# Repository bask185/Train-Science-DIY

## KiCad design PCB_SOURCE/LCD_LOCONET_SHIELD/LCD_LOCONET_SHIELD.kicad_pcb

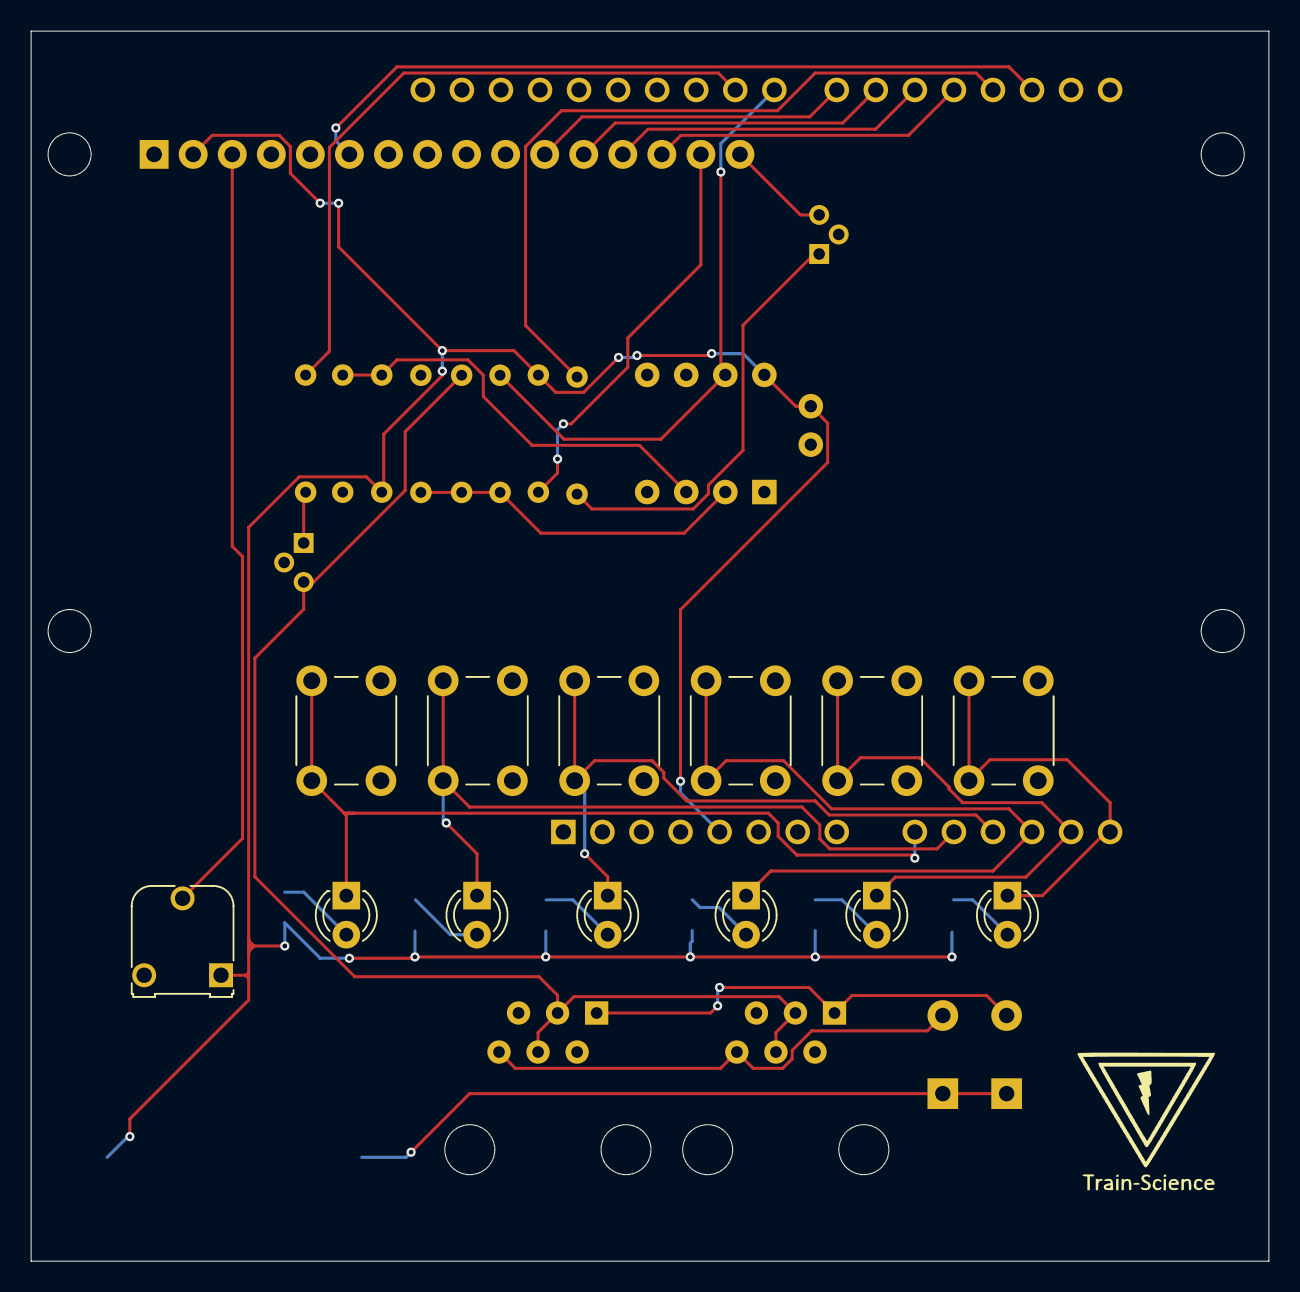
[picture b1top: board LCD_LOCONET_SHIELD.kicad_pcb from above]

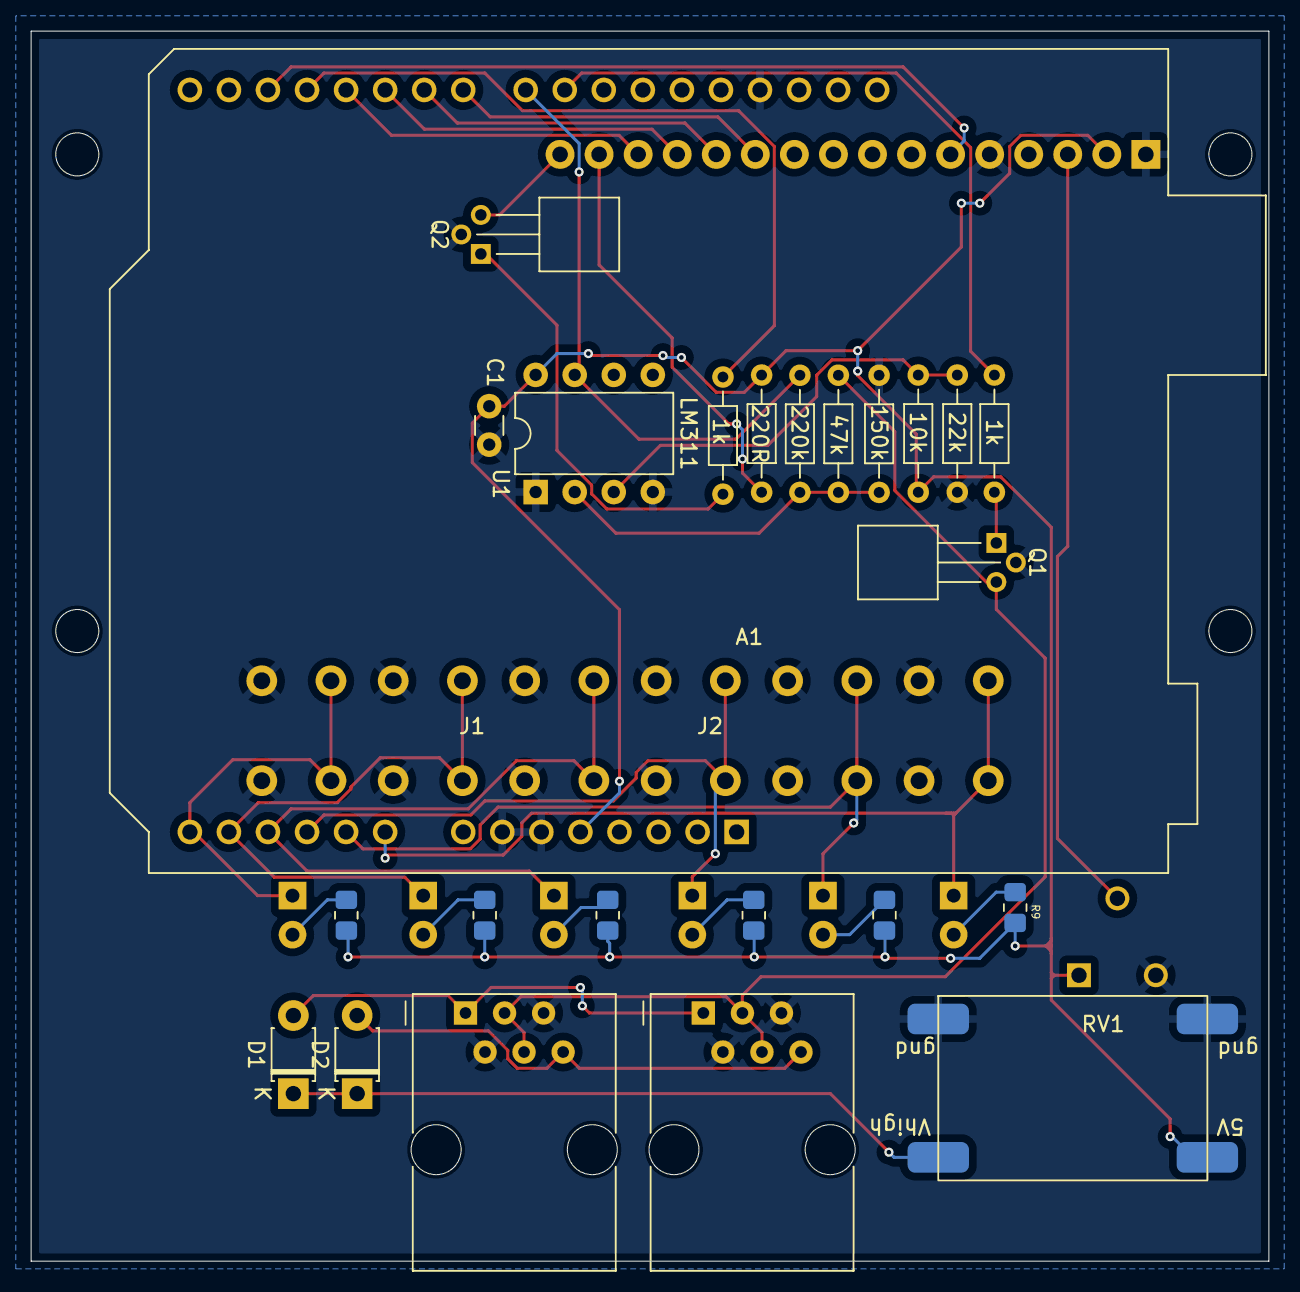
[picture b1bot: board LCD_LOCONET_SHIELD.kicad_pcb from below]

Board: 2 copper layers, 80.5 x 80.0 mm, 38 parts (24 on the bottom side), 33 nets.

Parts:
A1: Arduino_UNO_R3
C1: 100nF; C_Disc_D3.0mm_W1.6mm_P2.50mm
D1, D2: SM4007; D_T-1_P5.08mm_Horizontal
D3, D4, D5, D6, D7, D8: LED; LED_D3.0mm
J1, J2: RJ12
Q1, Q2: NPN_TOR; TO-92_Horizontal1
R1: 47k; R_Axial_DIN0204_L3.6mm_D1.6mm_P7.62mm_Horizontal
R2: 150k; R_Axial_DIN0204_L3.6mm_D1.6mm_P7.62mm_Horizontal
R3: 10k; R_Axial_DIN0204_L3.6mm_D1.6mm_P7.62mm_Horizontal
R4: 22k; R_Axial_DIN0204_L3.6mm_D1.6mm_P7.62mm_Horizontal
R5, R7: 1k; R_Axial_DIN0204_L3.6mm_D1.6mm_P7.62mm_Horizontal
R6: 220k; R_Axial_DIN0204_L3.6mm_D1.6mm_P7.62mm_Horizontal
R8: 220R; R_Axial_DIN0204_L3.6mm_D1.6mm_P7.62mm_Horizontal
R9, R10, R11, R12, R13, R14: 470R; R_0805_handsolder-smalltext
RV1: R_Potentiometer; Potentiometer_Runtron_RM-065_Vertical
SW1, SW2, SW3, SW4, SW5, SW6: SW_Push; SW_PUSH_6mm_H4.3mm
U1: LM311; DIP-8_W7.62mm
U2: Buck
U3: LCD-16X2; LCD-16X2_NOSILK

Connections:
+5V: A1.5 (+5V), C1.1, R3.1, R8.2, R9.2, R10.2, R11.2, R12.2, R13.2, R14.2, RV1.1, U1.8 (V+), U2.1 (5V), U3.2 (VDD)
+12V: D1.1 (K), D2.1 (K), U2.4 (in+)
/D4: A1.22 (D7), U3.11 (DB4)
/D5: A1.21 (D6), U3.12 (DB5)
/D6: A1.20 (D5), U3.13 (DB6)
/D7: A1.19 (D4), U3.14 (DB7)
/Lnet_Rx: A1.23 (D8), R6.2, U1.7
/Lnet_Tx: A1.24 (D9), R5.2
/background: A1.18 (D3), R7.2
/enabele: A1.17 (D2), U3.6 (E)
GND: A1.6 (GND), A1.7 (GND), A1.29 (GND), C1.2, J1.2, J1.5, J2.2, J2.5, Q1.2 (E), Q2.2 (E), R2.2, R4.1, RV1.3, SW1.2, SW2.2, SW3.2, SW4.2, SW5.2, SW6.2, U1.1 (GND), U1.4 (V-), U2.2 (gnd), U2.3 (gnd), U3.1 (VSS), U3.5 (R/W)
unnamed: A1.9 (A0), D3.1 (K), SW1.1
unnamed: A1.10 (A1), D4.1 (K), SW2.1
unnamed: A1.11 (A2), D5.1 (K), SW3.1
unnamed: A1.12 (A3), D6.1 (K), SW4.1
unnamed: D1.2 (A), J1.1, J2.1
unnamed: D2.2 (A), J1.6, J2.6
unnamed: D3.2 (A), R9.1
unnamed: D4.2 (A), R10.1
unnamed: D5.2 (A), R11.1
unnamed: D6.2 (A), R12.1
unnamed: D7.2 (A), R13.1
unnamed: A1.13 (SDA/A4), D7.1 (K), SW5.1
unnamed: D8.2 (A), R14.1
unnamed: A1.14 (SCL/A5), D8.1 (K), SW6.1
unnamed: Q1.1 (B), R5.1
unnamed: J1.3, J1.4, J2.3, J2.4, Q1.3 (C), R1.1
unnamed: Q2.1 (B), R7.1
unnamed: Q2.3 (C), U3.16 (K)
unnamed: R1.2, R2.1, R6.1, U1.2 (+)
unnamed: R3.2, R4.2, U1.3 (-)
unnamed: R8.1, U3.15 (A)
unnamed: RV1.2, U3.3 (VO)

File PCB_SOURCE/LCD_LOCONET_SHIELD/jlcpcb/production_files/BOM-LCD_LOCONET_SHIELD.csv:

Comment,Designator,Footprint,LCSC
470R,"R10,R11,R12,R13,R14,R9",R_0805_handsolder-smalltext,C17710
1k,"R5,R7,R8",R_Axial_DIN0204_L3.6mm_D1.6mm_P7.62mm_Horizontal,C21190
NPN_TOR,"Q1,Q2",TO-92_Horizontal1,C2145
150k,R2,R_Axial_DIN0204_L3.6mm_D1.6mm_P7.62mm_Horizontal,C22807
220k,R6,R_Axial_DIN0204_L3.6mm_D1.6mm_P7.62mm_Horizontal,C22961
10k,R3,R_Axial_DIN0204_L3.6mm_D1.6mm_P7.62mm_Horizontal,C25804
47k,R1,R_Axial_DIN0204_L3.6mm_D1.6mm_P7.62mm_Horizontal,C25819
100nF,C1,C_Disc_D3.0mm_W1.6mm_P2.50mm,C307331
22k,R4,R_Axial_DIN0204_L3.6mm_D1.6mm_P7.62mm_Horizontal,C31850
LM311,U1,DIP-8_W7.62mm,C434495
SM4007,"D1,D2",D_T-1_P5.08mm_Horizontal,C64898
SW_Push,SW5,SW_PUSH_6mm_H4.3mm,
LCD-16X2,U3,LCD-16X2_NOSILK,
LED,D3,LED_D3.0mm,
LED,D4,LED_D3.0mm,
R_Potentiometer,RV1,Potentiometer_Runtron_RM-065_Vertical,
LED,D8,LED_D3.0mm,
LED,D5,LED_D3.0mm,
LED,D7,LED_D3.0mm,
SW_Push,SW3,SW_PUSH_6mm_H4.3mm,
SW_Push,SW6,SW_PUSH_6mm_H4.3mm,
SW_Push,SW2,SW_PUSH_6mm_H4.3mm,
LED,D6,LED_D3.0mm,
SW_Push,SW4,SW_PUSH_6mm_H4.3mm,
SW_Push,SW1,SW_PUSH_6mm_H4.3mm,
RJ12,J1,RJ12,
Arduino_UNO_R3,A1,Arduino_UNO_R3,
RJ12,J2,RJ12,
Buck,U2,Buck,

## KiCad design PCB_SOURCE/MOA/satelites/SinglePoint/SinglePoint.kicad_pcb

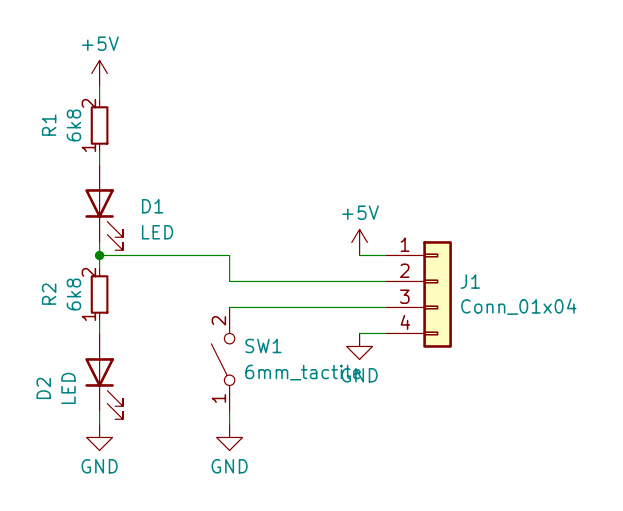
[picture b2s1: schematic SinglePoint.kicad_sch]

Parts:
D1, D2: LED; LED_D3.0mm; JLCPCB Part# C779430
J1: Conn_01x04; JST_SH_SM04B-SRSS-TB_1x04-1MP_P1.00mm_Horizontal; JLCPCB Part# C265102
R1, R2: 6k8; R_0603_smalltext; JLCPCB Part# C23212
SW1: 6mm_tactile; tactile_SMD_6mm; JLCPCB Part# C589249

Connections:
+5V: J1.1, R1.2
GND: D2.1 (K), J1.4, SW1.1 (A)
unnamed: D1.2 (A), R1.1
unnamed: D1.1 (K), J1.2, R2.2
unnamed: D2.2 (A), R2.1
unnamed: J1.3, SW1.2 (B)

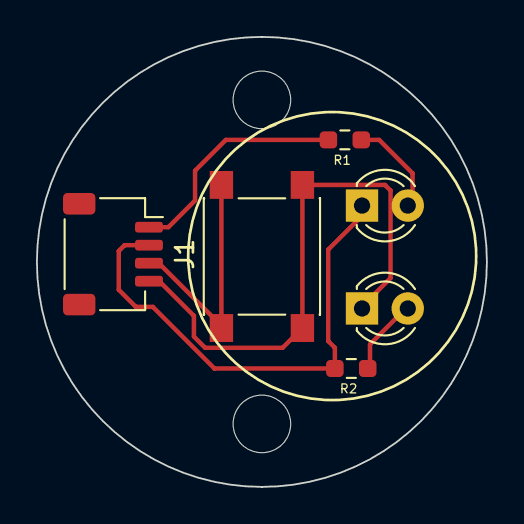
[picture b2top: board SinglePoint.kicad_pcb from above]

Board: 2 copper layers, 25.0 x 25.0 mm, 6 parts (0 on the bottom side), 6 nets.

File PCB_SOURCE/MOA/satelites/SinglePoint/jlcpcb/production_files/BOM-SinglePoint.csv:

Comment,Designator,Footprint,LCSC
6k8,"R1,R2",R_0603_smalltext,C23212
Conn_01x04,J1,JST_SH_SM04B-SRSS-TB_1x04-1MP_P1.00mm_Horizontal,C265102
6mm_tactile,SW1,tactile_SMD_6mm,C589249

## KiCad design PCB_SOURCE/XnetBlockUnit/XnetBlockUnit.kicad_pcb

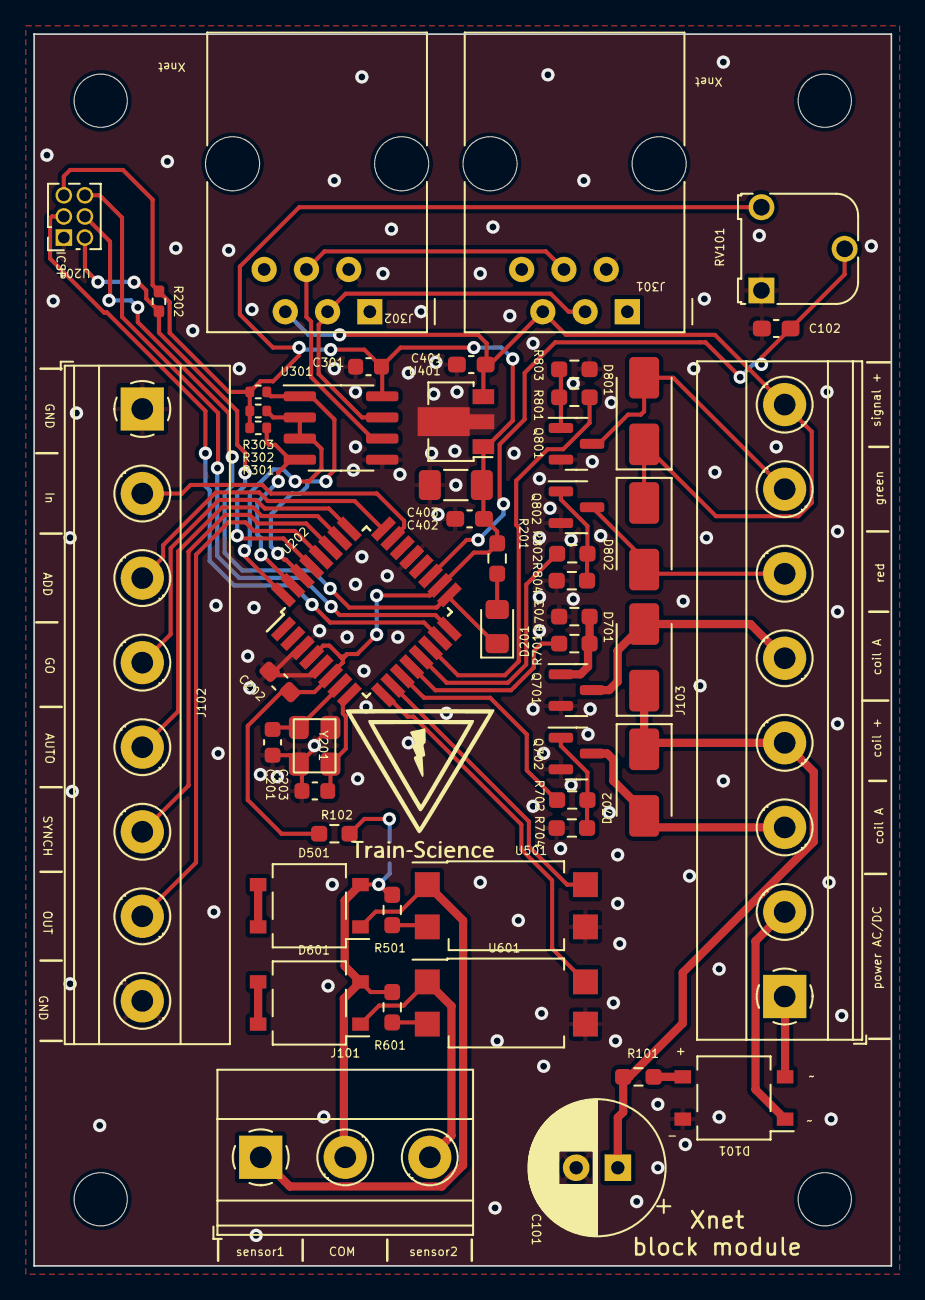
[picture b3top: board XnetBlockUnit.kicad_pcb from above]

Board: 2 copper layers, 51.5 x 74.0 mm, 52 parts (1 on the bottom side), 48 nets.

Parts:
C101: 2000uF; CP_Radial_D8.0mm_P2.50mm
C102, C202, C402: 100nF; C_0603_1608Metric_Pad1.08x0.95mm_HandSolder
C201, C203: 12pF; C_0603_1608Metric
C301: 100nF; C_0603_1608Metric
C401: 330nF; C_0603_1608Metric_Pad1.08x0.95mm_HandSolder
C403: 100uF; C_1206_3216Metric_Pad1.33x1.80mm_HandSolder
D101, D501, D601: MB6S; TO-269AA
D201: LED; LED_0805_2012Metric_Pad1.15x1.40mm_HandSolder
D701, D702, D801, D802: D_SMA
J101: sensor; TerminalBlock_Phoenix_MKDS-1,5-3-5.08_1x03_P5.08mm_Horizont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
J102, J103: Screw_Terminal_01x08; TerminalBlock_Phoenix_MKDS-1,5-8-5.08_1x08_P5.08mm_Horizont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
J301, J302: RJ12
JP101: SolderJumper_2_Open; SolderJumper-2_P1.3mm_Open_RoundedPad1.0x1.5mm
Q701, Q702, Q801, Q802: SOT-23
R101: 100R; R_0603_smalltext
R102: 1k; R_0603_smalltext
R201: 6k2; R_0603_1608Metric_Pad0.98x0.95mm_HandSolder
R202: 10k; R_0402_1005Metric_Pad0.72x0.64mm_HandSolder
R301, R302, R303: 10k; R_0402_1005Metric
R501, R601: 47k; R_0603_smalltext
R701, R702, R703, R704, R801, R802, R803, R804: R_0603_1608Metric_Pad0.98x0.95mm_HandSolder
RV101: R_Potentiometer; Potentiometer_Runtron_RM-065_Vertical
U201: HEADER_3x2; PinSocket_2x03_P1.27mm_Vertical
U202: ATmega328-A; TQFP-32_7x7mm_P0.8mm
U301: MAX485E; SOIC-8_3.9x4.9mm_P1.27mm
U401: L78L05_SOT89; SOT-89-3
U501, U601: EL814; SSO-4_6.7x5.1mm_P2.54mm_Clearance8mm
Y201: Crystal_GND2; crystal_arduino

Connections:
+5V: C202.2, C301.1, C402.1, C403.1, R102.1, R201.1, R202.1, R301.1, R302.1, R303.1, RV101.3, U201.5, U202.4 (VCC), U202.6 (VCC), U202.18 (AVCC), U301.8 (VCC), U401.1 (OUT)
+12V: C401.1, D801.1 (K), D802.1 (K), J103.8, J301.5, J302.5, U401.3 (IN)
/AC1: D101.1, J103.2
/AC2: D101.2, J103.1
/In: J102.2, U202.23 (PC0)
/Out: J102.7, U202.28 (PC5)
/Xnet/A: J301.4, J302.4, U301.6 (A)
/Xnet/B: J301.3, J302.3, U301.7 (B)
/Xnet/RS485_DIR: R302.2, U202.32 (PD2), U301.2 (~RE), U301.3 (DE)
/Xnet/Rx: R303.2, U202.30 (PD0), U301.1 (RO)
/Xnet/Tx: R301.2, U202.31 (PD1), U301.4 (DI)
/add: J102.3, U202.24 (PC1)
/atmega/A6: C102.2, RV101.2, U202.19 (ADC6)
/atmega/LED: D201.1 (K), U201.4, U202.17 (PB5)
/atmega/MISO: U201.6, U202.16 (PB4)
/atmega/MOSI: U201.3, U202.15 (PB3)
/atmega/X1: C201.2, U202.7 (XTAL1/PB6), Y201.1
/atmega/X2: C203.2, U202.8 (XTAL2/PB7), Y201.3
/atmega/reset: R202.2, U201.2, U202.29 (~RESET/PC6)
/auto: J102.5, U202.26 (PC3)
/coil_A: D701.2 (A), J103.5, Q701.3 (D)
/coil_A_TTL: R702.1, U202.11 (PD7)
/coil_B: D702.2 (A), J103.3, Q702.3 (D)
/coil_B_TTL: R701.1, U202.12 (PB0)
/coil_pow: C101.1, D701.1 (K), D702.1 (K), J103.4, R101.1
/go: J102.4, U202.25 (PC2)
/green: D801.2 (A), J103.7, Q801.3 (D)
/red: D802.2 (A), J103.6, Q802.3 (D)
/sens_1: U202.10 (PD6), U501.4
/sens_2: U202.9 (PD5), U601.4
/sensor1/COM: D501.2, D601.2, J101.2, JP101.1 (A), R501.2, R601.2
/sensor1/TRACK: D501.1, J101.1, U501.1
/sensor2/TRACK: D601.1, J101.3, U601.1
/signal_R: R801.1, U202.14 (PB2)
/signal_g: R802.1, U202.13 (PB1)
/synch: J102.6, U202.27 (PC4)
GND: C101.2, C102.1, C201.1, C202.1, C203.1, C301.2, C401.2, C402.2, C403.2, D101.4 (-), J102.1, J102.8, J301.2, J302.2, Q701.2 (S), Q702.2 (S), Q801.2 (S), Q802.2 (S), R703.1, R704.1, R803.1, R804.1, RV101.1, U201.1, U202.3 (GND), U202.5 (GND), U202.21 (GND), U301.5 (GND), U401.2 (GND), U501.3, U601.3, Y201.2 (GND), Y201.4 (GND)
unnamed: D101.3 (+), R101.2
unnamed: D201.2 (A), R201.2
unnamed: D501.3 (+), D501.4 (-)
unnamed: D601.3 (+), D601.4 (-)
unnamed: JP101.2 (B), R102.2
unnamed: Q701.1 (G), R701.2, R703.2
unnamed: Q702.1 (G), R702.2, R704.2
unnamed: Q801.1 (G), R801.2, R803.2
unnamed: Q802.1 (G), R802.2, R804.2
unnamed: R501.1, U501.2
unnamed: R601.1, U601.2

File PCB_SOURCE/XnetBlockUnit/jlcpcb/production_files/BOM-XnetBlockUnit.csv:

Comment,Designator,Footprint,LCSC
Crystal_GND2,Y201,crystal_arduino,C13738
100nF,"C102,C202,C301,C402",C_0603_1608Metric_Pad1.08x0.95mm_HandSolder,C14663
ATmega328-A,U202,TQFP-32_7x7mm_P0.8mm,C14877
100uF,C403,C_1206_3216Metric_Pad1.33x1.80mm_HandSolder,C15008
330nF,C401,C_0603_1608Metric_Pad1.08x0.95mm_HandSolder,C1615
~,"Q701,Q702,Q801,Q802",SOT-23,C20917
1k,R102,R_0603_smalltext,C21190
100R,R101,R_0603_smalltext,C22775
~,"R701,R702,R801,R802",R_0603_1608Metric_Pad0.98x0.95mm_HandSolder,C23345
MB6S,"D101,D501,D601",TO-269AA,C2488
10k,"R202,R301,R302,R303",R_0402_1005Metric_Pad0.72x0.64mm_HandSolder,C25744
~,"R703,R704,R803,R804",R_0603_1608Metric_Pad0.98x0.95mm_HandSolder,C25804
47k,"R501,R601",R_0603_smalltext,C25819
12pF,"C201,C203",C_0603_1608Metric,C38523
6k2,R201,R_0603_1608Metric_Pad0.98x0.95mm_HandSolder,C4260
EL814,"U501,U601",SSO-4_6.7x5.1mm_P2.54mm_Clearance8mm,C500388
MAX485E,U301,SOIC-8_3.9x4.9mm_P1.27mm,C668206
L78L05_SOT89,U401,SOT-89-3,C71136
LED,D201,LED_0805_2012Metric_Pad1.15x1.40mm_HandSolder,C84256
~,"D701,D702,D801,D802",D_SMA,C8678
Screw_Terminal_01x08,J103,"TerminalBlock_Phoenix_MKDS-1,5-8-5.08_1x08_P5.08mm_Horizontal",
2000uF,C101,CP_Radial_D8.0mm_P2.50mm,
sensor,J101,"TerminalBlock_Phoenix_MKDS-1,5-3-5.08_1x03_P5.08mm_Horizontal",
HEADER_3x2,U201,PinSocket_2x03_P1.27mm_Vertical,
Screw_Terminal_01x08,J102,"TerminalBlock_Phoenix_MKDS-1,5-8-5.08_1x08_P5.08mm_Horizontal",
RJ12,J302,RJ12,
RJ12,J301,RJ12,
SolderJumper_2_Open,JP101,SolderJumper-2_P1.3mm_Open_RoundedPad1.0x1.5mm,
R_Potentiometer,RV101,Potentiometer_Runtron_RM-065_Vertical,

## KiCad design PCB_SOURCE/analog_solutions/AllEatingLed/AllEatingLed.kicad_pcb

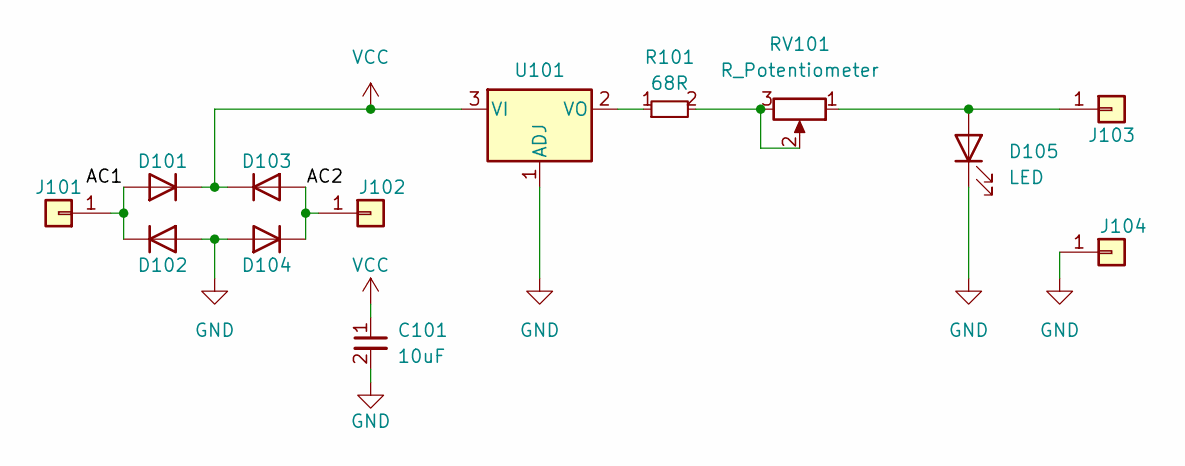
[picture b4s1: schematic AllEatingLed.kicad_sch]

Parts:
C101: 10uF; C_1206_3216Metric; JLCPCB Part# C89632
D101, D102, D103, D104: 1N4148WS; D_SOD-323; JLCPCB Part# C2128
D105: LED; LED_D3.0mm
J101, J102, J103, J104: Conn_01x01; SolderWirePad_1x01_SMD_1x2mm
R101: 68R; R_0603_smalltext; JLCPCB Part# C27592
RV101: R_Potentiometer; Potentiometer_Bourns_TC33X_Vertical; JLCPCB Part# C128548
U101: LM317_SOT-223; SOT-223-3_TabPin2; JLCPCB Part# C347367

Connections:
/AC1: D101.2 (A), D102.1 (K), J101.1
/AC2: D103.2 (A), D104.1 (K), J102.1
GND: C101.2, D102.2 (A), D104.2 (A), D105.1 (K), J104.1, U101.1 (ADJ)
unnamed: D105.2 (A), J103.1, RV101.1
unnamed: R101.2, RV101.2, RV101.3
unnamed: R101.1, U101.2 (VO)
VCC: C101.1, D101.1 (K), D103.1 (K), U101.3 (VI)

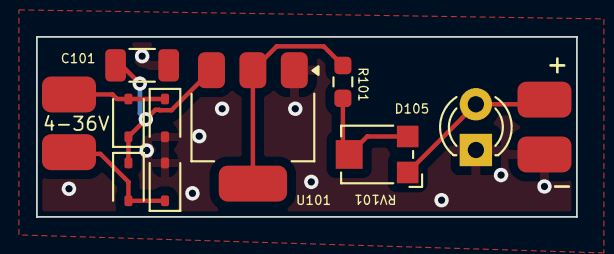
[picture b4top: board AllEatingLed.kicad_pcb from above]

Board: 2 copper layers, 30.0 x 10.0 mm, 13 parts (0 on the bottom side), 7 nets.

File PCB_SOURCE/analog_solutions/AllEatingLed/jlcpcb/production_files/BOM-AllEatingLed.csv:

Comment,Designator,Footprint,LCSC
R_Potentiometer,RV101,Potentiometer_Bourns_TC33X_Vertical,C128548
1N4148WS,"D101,D102,D103,D104",D_SOD-323,C2128
68R,R101,R_0603_smalltext,C27592
LM317_SOT-223,U101,SOT-223-3_TabPin2,C347367
10uF,C101,C_1206_3216Metric,C89632
